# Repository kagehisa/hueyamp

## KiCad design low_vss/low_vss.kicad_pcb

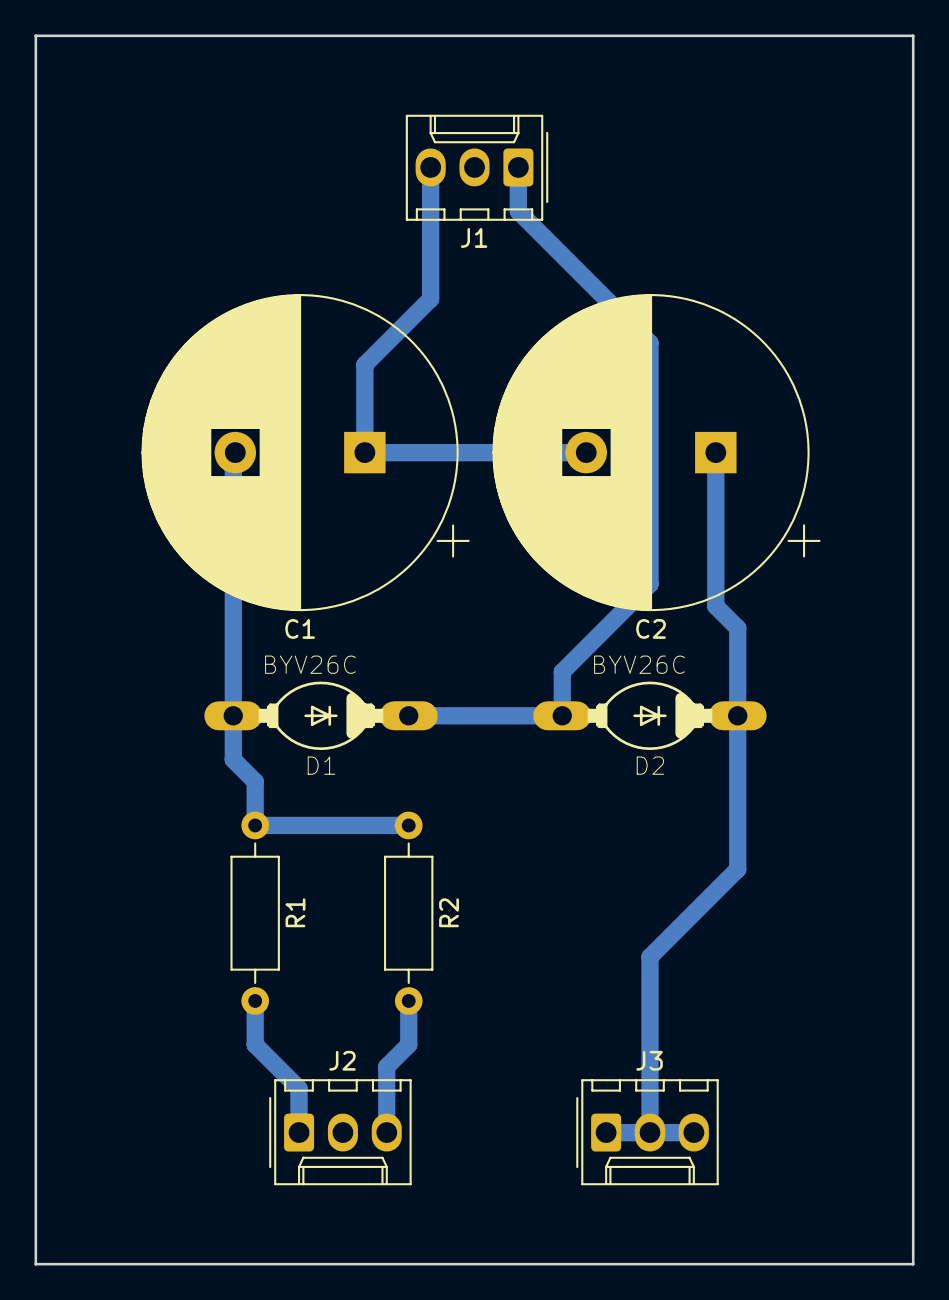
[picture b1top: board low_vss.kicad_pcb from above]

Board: 2 copper layers, 50.8 x 71.1 mm, 9 parts (0 on the bottom side), 6 nets.

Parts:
C1, C2: 4700uF 25V Elko; CP_Radial_D18.0mm_P7.50mm
D1, D2: BYV26C; DO204-10
J1, J2, J3: Conn_01x03_Male; Molex_KK-254_AE-6410-03A_1x03_P2.54mm_Vertical
R1, R2: 470R; R_Axial_DIN0207_L6.3mm_D2.5mm_P10.16mm_Horizontal

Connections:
GNDREF: C2.1, D2.2, J3.1, J3.2, J3.3
unnamed: C1.1, C2.2, J1.3
unnamed: C1.2, D1.1, R1.1, R2.1
unnamed: D1.2, D2.1, J1.1
unnamed: J2.1, R1.2
unnamed: J2.3, R2.2

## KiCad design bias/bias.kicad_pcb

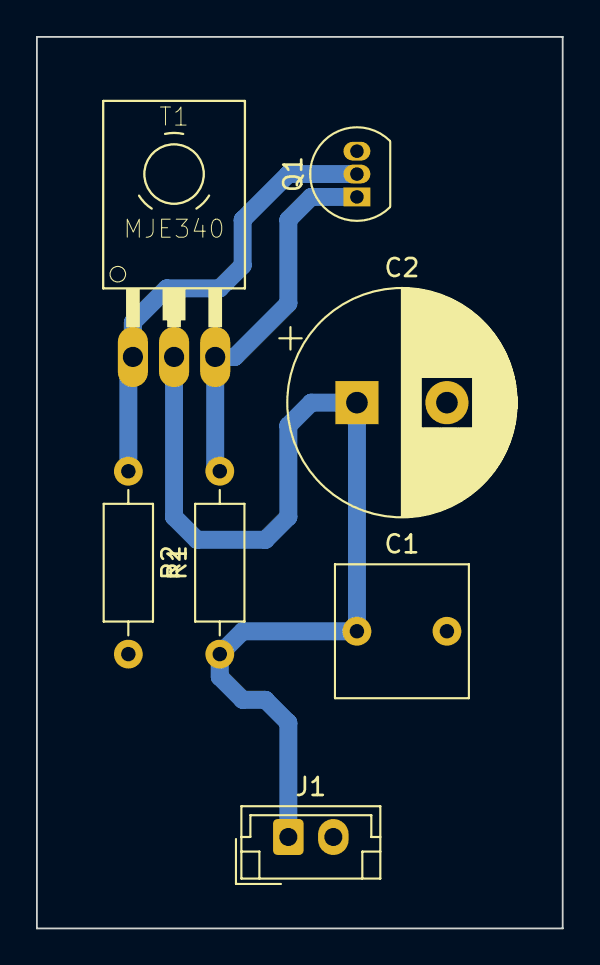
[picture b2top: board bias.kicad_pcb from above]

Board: 2 copper layers, 29.2 x 49.5 mm, 7 parts (0 on the bottom side), 4 nets.

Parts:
C1: 1uF 63V SMR (PPS); C_Rect_L7.2mm_W7.2mm_P5.00mm_FKS2_FKP2_MKS2_MKP2
C2: 470uF 50V BG; CP_Radial_D12.5mm_P5.00mm
J1: Conn_01x02; JST_EH_B02B-EH-A_1x02_P2.50mm_Vertical
Q1: BC547; TO-92_Inline
R1: 5k6; R_Axial_DIN0207_L6.3mm_D2.5mm_P10.16mm_Horizontal
R2: 16R; R_Axial_DIN0207_L6.3mm_D2.5mm_P10.16mm_Horizontal
T1: MJE340; TO126

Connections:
GND: C1.2, C2.2, J1.2, Q1.3, R2.2
unnamed: Q1.1, R1.2, T1.3
unnamed: Q1.2, R2.1, T1.1
VCC: C1.1, C2.1, J1.1, R1.1, T1.2

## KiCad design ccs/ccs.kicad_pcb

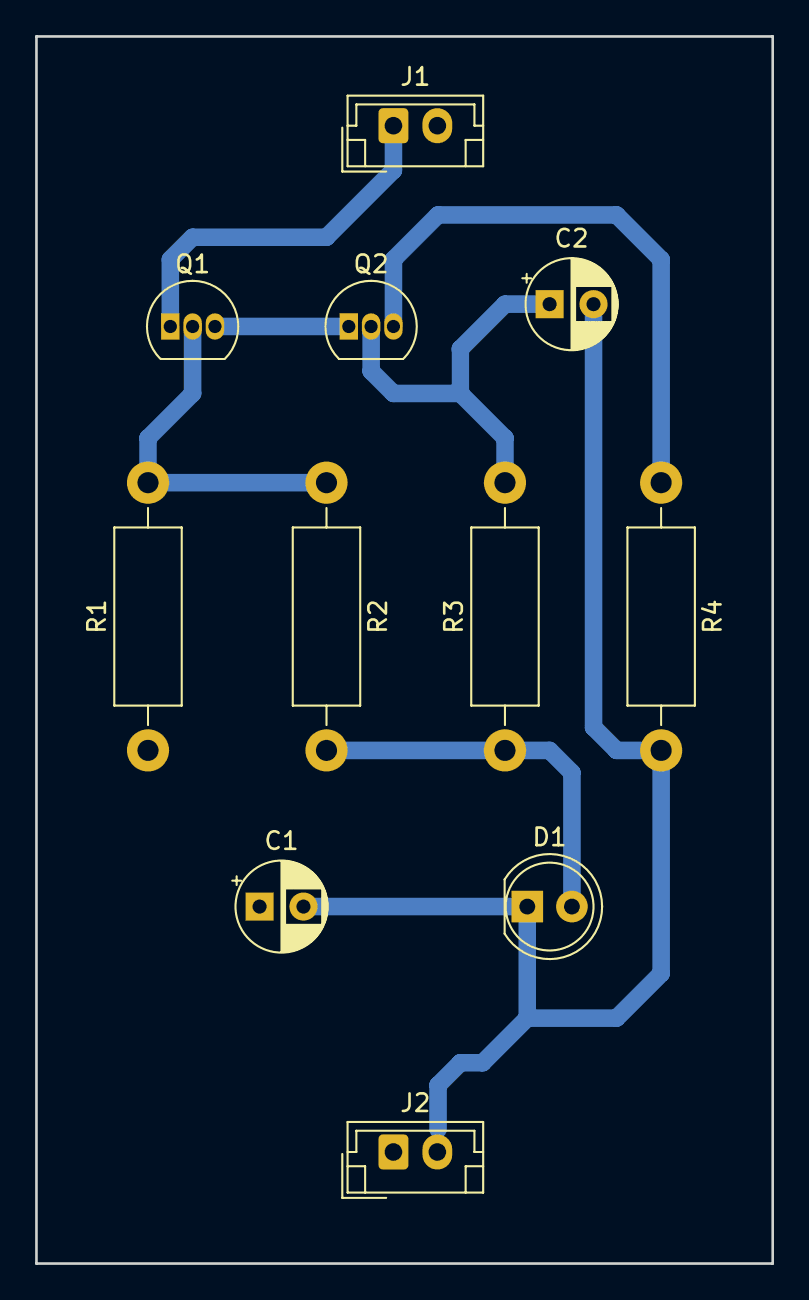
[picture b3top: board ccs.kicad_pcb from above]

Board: 2 copper layers, 41.9 x 69.8 mm, 11 parts (0 on the bottom side), 8 nets.

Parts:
C1: 47uF 35V BG; CP_Radial_D5.0mm_P2.50mm
C2: 22uF 35VBlackgate NX; CP_Radial_D5.0mm_P2.50mm
D1: LED; LED_D5.0mm
J1: Conn_01x01_Male; JST_EH_B02B-EH-A_1x02_P2.50mm_Vertical
J2: Conn_01x02_Male; JST_EH_B02B-EH-A_1x02_P2.50mm_Vertical
Q1, Q2: BC547; TO-92_Inline
R1: 1k6; R_Axial_DIN0411_L9.9mm_D3.6mm_P15.24mm_Horizontal
R2, R4: 1k; R_Axial_DIN0411_L9.9mm_D3.6mm_P15.24mm_Horizontal
R3: 470R; R_Axial_DIN0411_L9.9mm_D3.6mm_P15.24mm_Horizontal

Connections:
GNDA: C1.1, J2.1, R1.1
unnamed: C2.1, Q2.2, R3.2
unnamed: D1.2, R2.2, R3.1
unnamed: Q1.2, R1.2, R2.1
unnamed: Q1.3, Q2.1
unnamed: Q2.3, R4.1
VCC: C1.2, C2.2, D1.1, J2.2, R4.2
VDDA: J1.1, Q1.1

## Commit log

2018-10-17 initial commit of ccs and bias boards for huey amp build
2018-10-30 low voltage nt added
